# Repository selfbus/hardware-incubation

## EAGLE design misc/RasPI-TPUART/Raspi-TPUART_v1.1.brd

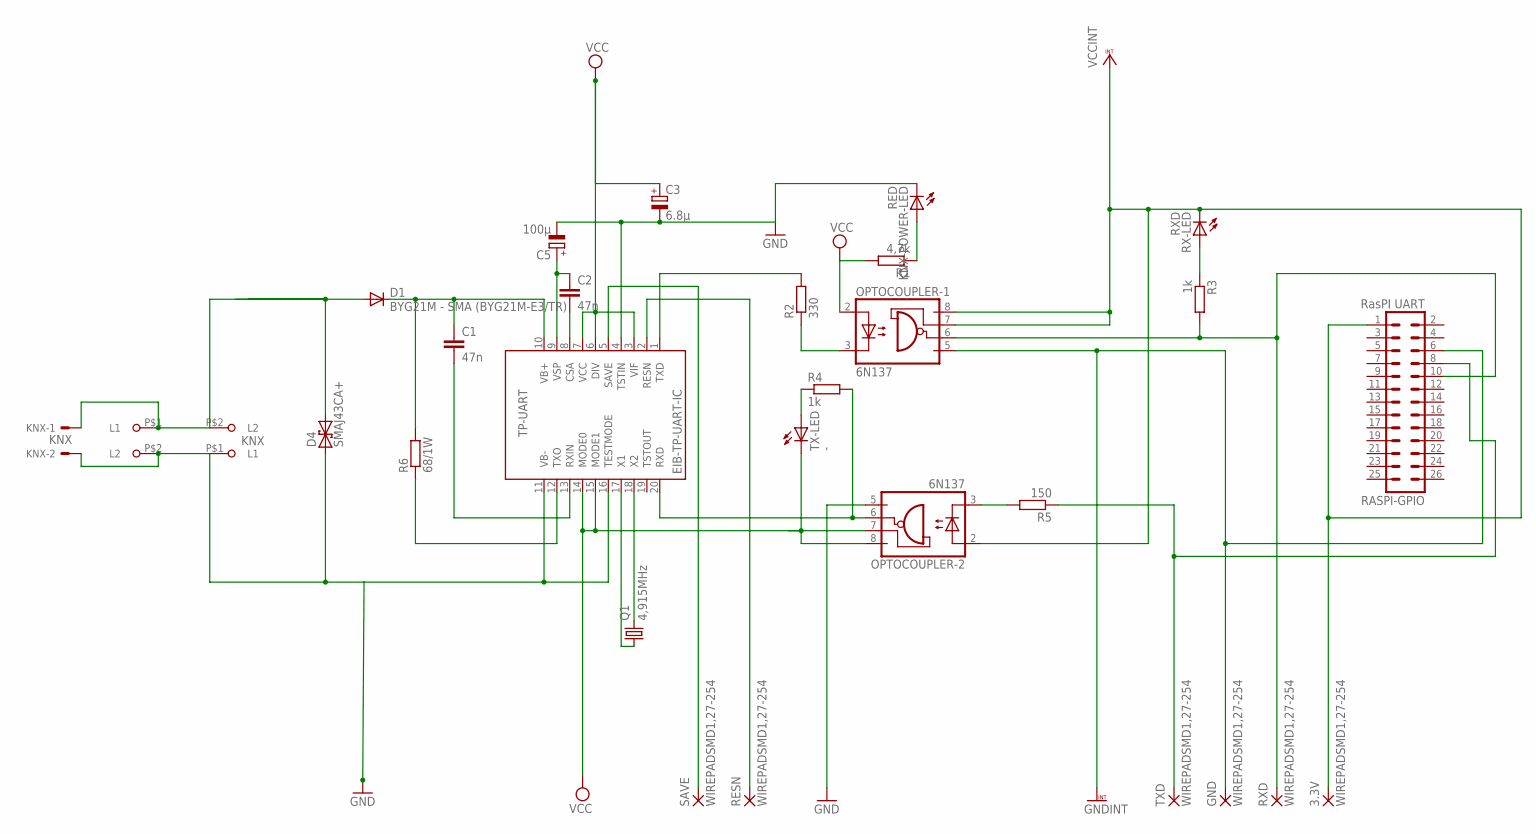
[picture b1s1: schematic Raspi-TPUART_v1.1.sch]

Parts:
3.3V: WIREPADSMD1,27-254; SMD1,27-2,54
C1, C2: 47n; C1206
C3: 6.8µ; CT7343
C5: 100µ; CT7343
D1: BYG21M - SMA (BYG21M-E3/TR); SMB
D4: SMAJ43CA+; DO214AA
EIB-TP-UART-IC: TP-UART; SOIC20
GND: WIREPADSMD1,27-254; SMD1,27-2,54
KNX: KNX; 22-23-2021
KNX-POWER-LED: RED; KA-3528ASYC
KNX_WAGO_243: 243-211
OPTOCOUPLER-1, OPTOCOUPLER-2: 6N137; DIL8-SMD
Q1: 4,915MHz; HC49UP
R1: 4,7k; M1206
R2: 330; M1206
R3, R4: 1k; M1206
R5: 150; M1206
R6: 68/1W; R2512
RASPI-GPIO: RasPI UART; MA13-2
RESN: WIREPADSMD1,27-254; SMD1,27-2,54
RX-LED: RXD; KA-3528ASYC
RXD: WIREPADSMD1,27-254; SMD1,27-2,54
SAVE: WIREPADSMD1,27-254; SMD1,27-2,54
TX-LED: -; KA-3528ASYC
TXD: WIREPADSMD1,27-254; SMD1,27-2,54
U$1: 243-211

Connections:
CSA: C2.2, EIB-TP-UART-IC.8 (CSA)
GND: C3.-, C5.-, D4.A (1), EIB-TP-UART-IC.4 (TSTIN), EIB-TP-UART-IC.11 (VB-), EIB-TP-UART-IC.16 (TESTMODE), KNX.2, KNX-POWER-LED.C, KNX_WAGO_243.P$1 (L1), OPTOCOUPLER-2.5 (GND), U$1.P$2 (L2)
GNDINT: GND.1, OPTOCOUPLER-1.5 (GND), RASPI-GPIO.6
KNX+: D1.A, D4.C (2), KNX.1, KNX_WAGO_243.P$2 (L2), U$1.P$1 (L1)
unnamed: R3.1, RX-LED.A
unnamed: R4.1, TX-LED.A
unnamed: OPTOCOUPLER-2.3 (C), R5.2
unnamed: KNX-POWER-LED.A, R1.1
RASPI_RXD: OPTOCOUPLER-1.6 (VO), R3.2, RASPI-GPIO.10, RXD.1
RASPI_TXD: R5.1, RASPI-GPIO.8, TXD.1
RESN: EIB-TP-UART-IC.2 (RESN), RESN.1
RXD: EIB-TP-UART-IC.20 (RXD), OPTOCOUPLER-2.6 (VO), R4.2
RXIN: C1.2, EIB-TP-UART-IC.13 (RXIN)
SAVE: EIB-TP-UART-IC.5 (SAVE), SAVE.1
TXD: EIB-TP-UART-IC.1 (TXD), R2.2
TXD1: OPTOCOUPLER-1.3 (C), R2.1
TXO: EIB-TP-UART-IC.12 (TXO), R6.1
VB+: C1.1, D1.C, EIB-TP-UART-IC.10 (VB+), R6.2
VCC: C3.+, EIB-TP-UART-IC.3 (VIF), EIB-TP-UART-IC.6 (DIV), EIB-TP-UART-IC.7 (VCC), EIB-TP-UART-IC.14 (MODE0), EIB-TP-UART-IC.15 (MODE1), OPTOCOUPLER-1.2 (A), OPTOCOUPLER-2.7 (VE), OPTOCOUPLER-2.8 (VCC), R1.2, TX-LED.C
VCCINT: 3.3V.1, OPTOCOUPLER-1.7 (VE), OPTOCOUPLER-1.8 (VCC), OPTOCOUPLER-2.2 (A), RASPI-GPIO.1, RX-LED.C
VSP: C2.1, C5.+, EIB-TP-UART-IC.9 (VSP)
X1: EIB-TP-UART-IC.17 (X1), Q1.1
X2: EIB-TP-UART-IC.18 (X2), Q1.2

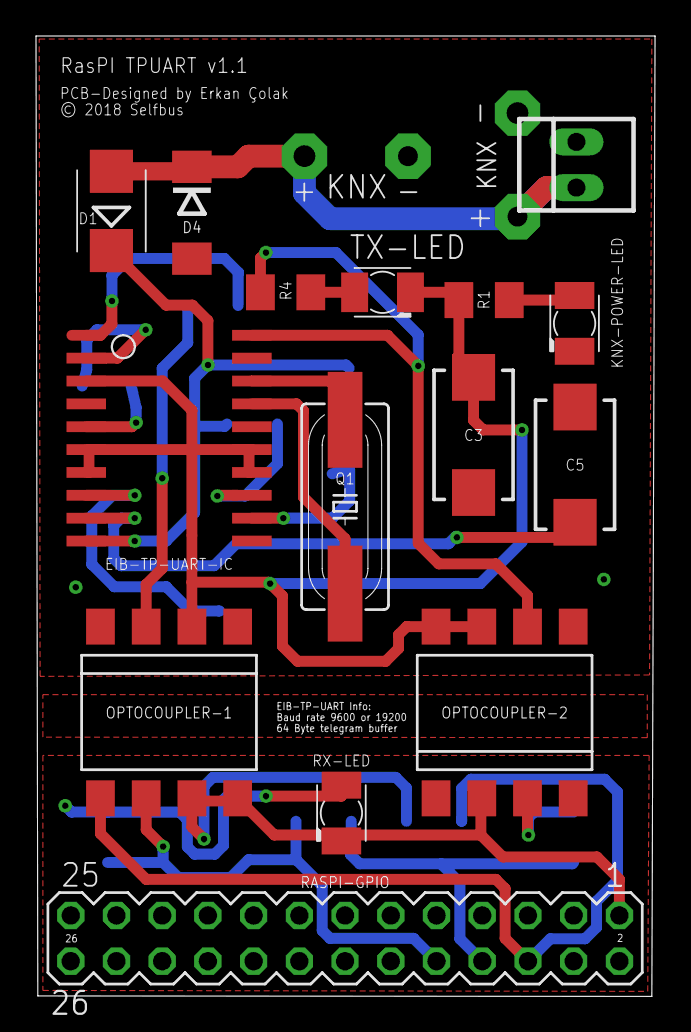
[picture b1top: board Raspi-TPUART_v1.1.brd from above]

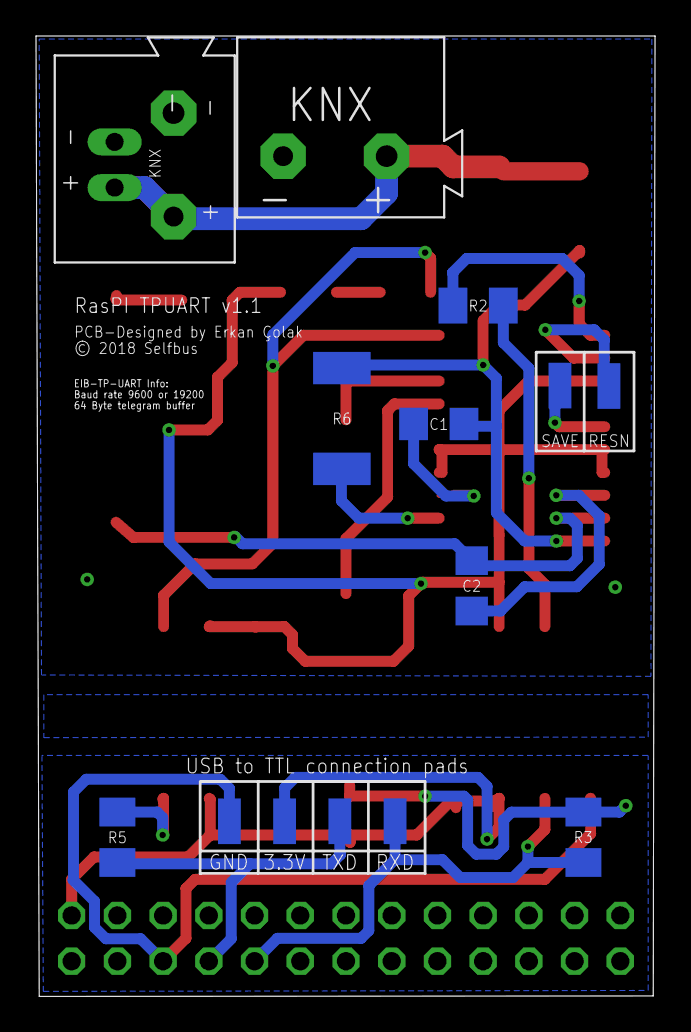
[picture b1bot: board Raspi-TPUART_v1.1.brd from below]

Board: 2 copper layers, 34.4 x 53.4 mm, 29 parts (14 on the bottom side), 23 nets.

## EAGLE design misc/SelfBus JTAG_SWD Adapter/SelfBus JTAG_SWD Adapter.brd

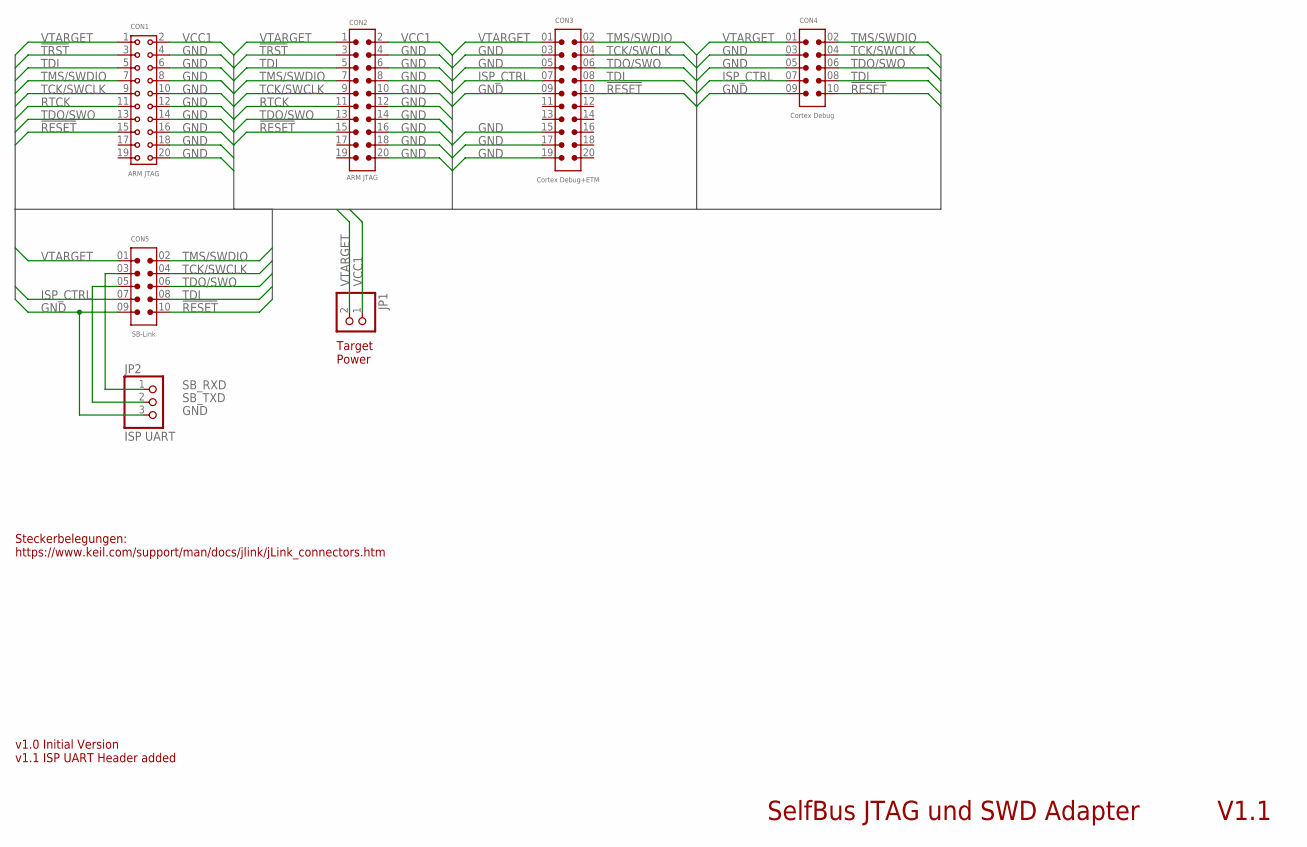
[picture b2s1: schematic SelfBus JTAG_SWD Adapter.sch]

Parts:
CON1: ARM JTAG; SAMTEC-SSQ-110-02-X-D-RA; MOUSER# 200-SSQ11002TDRA; LCSC2# C124406
CON2: ARM JTAG; 61202021721; MOUSER# 710-61202021721; LCSC3# C9144
CON3: Cortex Debug+ETM; SAMTEC_SHF-110-01-L-D-TH; MOUSER# 200-SHF11001LDTH
CON4: Cortex Debug; SAMTEC_SHF-105-01-X-D-TH; MOUSER# 200-SHF10501LDTH; LCSC2# C239059
CON5: SB-Link; SAMTEC-LTMM-105-02-T-D; MOUSER# 200-LTMM10502TD; LCSC3# C5661
JP1: Target Power; 1X02
JP2: ISP UART; 1X03

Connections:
!RESET: CON1.15, CON2.15, CON3.10, CON4.10, CON5.10
!TRST: CON1.3, CON2.3
GND: CON1.4, CON1.6, CON1.8, CON1.10, CON1.12, CON1.14, CON1.16, CON1.18, CON1.20, CON2.4, CON2.6, CON2.8, CON2.10, CON2.12, CON2.14, CON2.16, CON2.18, CON2.20, CON3.03 (3), CON3.05 (5), CON3.09 (9), CON3.15, CON3.17, CON3.19, CON4.03 (3), CON4.05 (5), CON4.09 (9), CON5.09 (9), JP2.3
ISP_CTRL: CON3.07 (7), CON4.07 (7), CON5.07 (7)
RTCK: CON1.11, CON2.11
SB_RXD: CON5.03 (3), JP2.1
SB_TXD: CON5.05 (5), JP2.2
TCK/SWCLK: CON1.9, CON2.9, CON3.04 (4), CON4.04 (4), CON5.04 (4)
TDI: CON1.5, CON2.5, CON3.08 (8), CON4.08 (8), CON5.08 (8)
TDO/SWO: CON1.13, CON2.13, CON3.06 (6), CON4.06 (6), CON5.06 (6)
TMS/SWDIO: CON1.7, CON2.7, CON3.02 (2), CON4.02 (2), CON5.02 (2)
VCC1: CON1.2, CON2.2, JP1.1
VTARGET: CON1.1, CON2.1, CON3.01 (1), CON4.01 (1), CON5.01 (1), JP1.2

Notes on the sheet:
SelfBus JTAG und SWD Adapter
V1.1
Target Power
Steckerbelegungen: https://www.keil.com/support/man/docs/jlink/jLink_connectors.htm
v1.0 Initial Version v1.1 ISP UART Header added

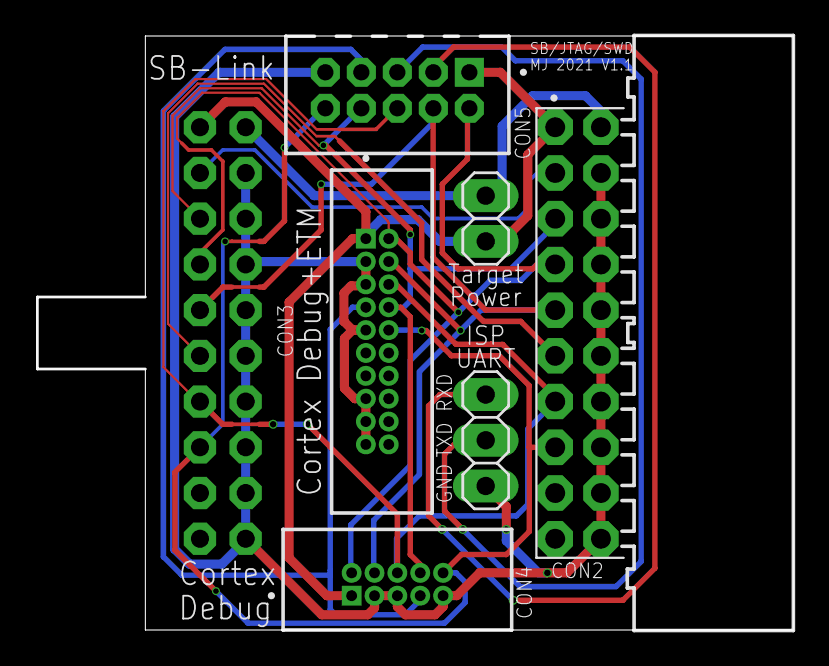
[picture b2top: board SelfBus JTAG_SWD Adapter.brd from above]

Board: 2 copper layers, 42.0 x 33.0 mm, 7 parts (1 on the bottom side), 13 nets.

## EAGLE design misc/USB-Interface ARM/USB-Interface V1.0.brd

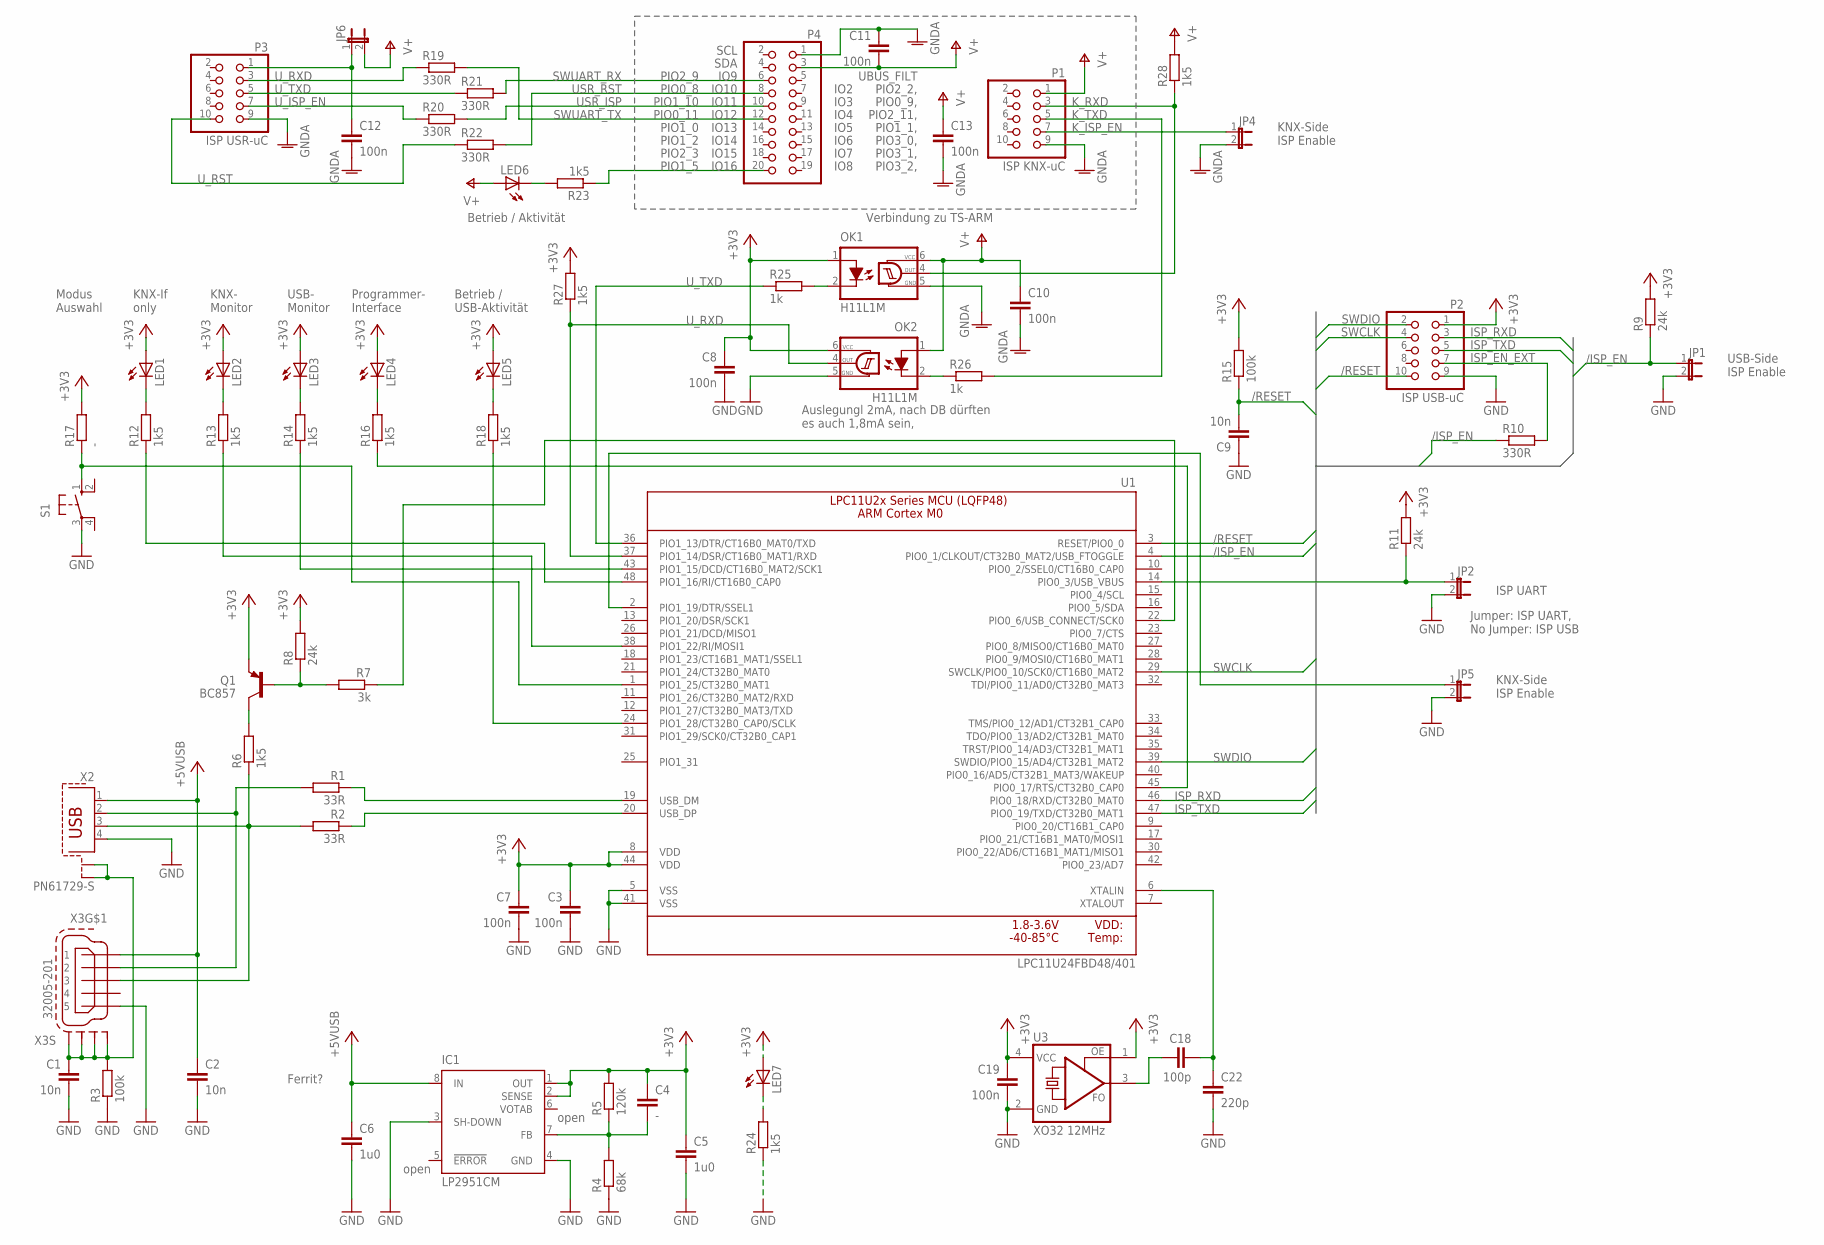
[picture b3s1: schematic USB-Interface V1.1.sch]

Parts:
C1, C2, C9: 10n; R0805M
C3, C7, C8, C10, C11, C12, C13, C19: 100n; R0805M
C4: -; R0805M
C5, C6: 1u0; R0805M
C18: 100p; R0805M
C22: 220p; R0805M
IC1: LP2951CM; SO08
JP1, JP2, JP4, JP5, JP6: JP1E; JP1
LED1, LED2, LED3, LED4, LED5, LED6, LED7: LEDSMT1206; 1206
OK1, OK2: H11L1M; DIL06S
P1: ISP KNX-uC; 2X05M
P2: ISP USB-uC; 2X05M
P3: ISP USR-uC; 2X05M
P4: PINHD-2X10/90; 2X10/90
Q1: BC857; SOT23-BEC
R1, R2: 33R; R0805M
R3, R15: 100k; R0805M
R4: 68k; R0805M
R5: 120k; R0805M
R6, R12, R13, R14, R16, R18, R23, R24, R27, R28: 1k5; R0805M
R7: 3k; R0805M
R8, R9, R11: 24k; R0805M
R10, R19, R20, R21, R22: 330R; R0805M
R17: -; R0805M
R25, R26: 1k; R0805M
S1: 10-XXSMD; B3F-10XX_SMD
U1: LPC11U24FBD48/401; LQFP48
U3: XO32 12MHz; ASF
X2: PN61729-S
X3: 32005-201

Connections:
+3V3: C3.1, C4.1, C5.1, C7.1, C8.1, C19.1, IC1.1 (OUT), IC1.2 (SENSE), LED1.A, LED2.A, LED3.A, LED4.A, LED5.A, LED7.A, OK1.1 (A), OK2.6 (VCC), P2.1, Q1.E, R5.2, R8.2, R9.2, R11.2, R15.2, R17.2, R27.2, U1.8 (VDD), U1.44 (VDD), U3.1 (OE), U3.4 (VCC)
+5V: C2.1, C6.1, IC1.8 (IN), X2.1, X3.1
/ISP_EN: JP1.1, R9.1, R10.1, U1.4 (PIO0_1/CLKOUT/CT32B0_MAT2/USB_FTOGGLE)
/RESET: C9.2, P2.10, R15.1, U1.3 (RESET/PIO0_0)
GND: C1.2, C2.2, C3.2, C5.2, C6.2, C7.2, C8.2, C9.1, C19.2, C22.2, IC1.3 (SH-DOWN), IC1.4 (GND), JP1.2, JP2.2, JP5.2, OK2.5 (GND), P2.9, R3.1, R4.1, R24.1, S1.3, U1.5 (VSS), U1.41 (VSS), U3.2 (GND), X2.4, X3.5
GNDA: C10.2, C11.1, C12.2, C13.2, JP4.2, OK1.5 (GND), P1.9, P3.9, P4.1
ISP_EN1: JP2.1, R11.1, U1.14 (PIO0_3/USB_VBUS)
ISP_EN_EXT: P2.7, R10.2
ISP_RXD: P2.3, U1.46 (PIO0_18/RXD/CT32B0_MAT0)
ISP_TXD: P2.5, U1.47 (PIO0_19/TXD/CT32B0_MAT1)
K_ISP_EN: JP4.1, P1.7
K_RXD: OK1.4 (OUT), P1.3, R28.1
K_TXD: P1.5, R26.2
unnamed: R1.1, U1.19 (USB_DM)
unnamed: R2.1, U1.20 (USB_DP)
unnamed: JP5.1, U1.2 (PIO1_19/DTR/SSEL1)
unnamed: R1.2, X2.2, X3.2
unnamed: R2.2, R6.1, X2.3, X3.3
unnamed: C1.1, R3.2, X2.S1, X2.S2, X3.M1 (S1), X3.M2 (S2), X3.M3 (S3), X3.M4 (S4)
unnamed: Q1.B, R7.2, R8.1
unnamed: C4.2, IC1.7 (FB), R4.2, R5.1
unnamed: Q1.C, R6.2
unnamed: R7.1, U1.22 (PIO0_6/USB_CONNECT/SCK0)
unnamed: LED6.C, R23.2
unnamed: P4.20, R23.1
unnamed: R17.1, S1.1 (S), U1.1 (PIO1_25/CT32B0_MAT1)
unnamed: LED1.C, R12.2
unnamed: LED2.C, R13.2
unnamed: C18.1, U3.3 (FO)
unnamed: LED3.C, R14.2
unnamed: LED4.C, R16.2
unnamed: R16.1, U1.45 (PIO0_17/RTS/CT32B0_CAP0)
unnamed: R14.1, U1.43 (PIO1_15/DCD/CT16B0_MAT2/SCK1)
unnamed: C18.2, C22.1, U1.6 (XTALIN)
unnamed: R13.1, U1.38 (PIO1_22/RI/MOSI1)
unnamed: R12.1, U1.48 (PIO1_16/RI/CT16B0_CAP0)
unnamed: LED7.C, R24.2
unnamed: R18.1, U1.24 (PIO1_28/CT32B0_CAP0/SCLK)
unnamed: LED5.C, R18.2
unnamed: P3.7, R20.1
unnamed: C12.1, JP6.1, P3.1
unnamed: OK1.2 (C), R25.2
unnamed: P3.10, R22.1
unnamed: P3.5, R21.1
unnamed: P3.3, R19.1
unnamed: OK2.2 (C), R26.1
SWCLK: P2.4, U1.29 (SWCLK/PIO0_10/SCK0/CT16B0_MAT2)
SWDIO: P2.2, U1.39 (SWDIO/PIO0_15/AD4/CT32B1_MAT2)
SWUART_RX: P4.6, R21.2
SWUART_TX: P4.12, R19.2
USR_ISP: P4.10, R20.2
USR_RST: P4.8, R22.2
U_RXD: OK2.4 (OUT), R27.1, U1.37 (PIO1_14/DSR/CT16B0_MAT1/RXD)
U_TXD: R25.1, U1.36 (PIO1_13/DTR/CT16B0_MAT0/TXD)
V+: C10.1, C11.2, C13.1, JP6.2, LED6.A, OK1.6 (VCC), OK2.1 (A), P1.1, P4.3, R28.2

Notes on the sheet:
open
Ferrit?
USB-Side ISP Enable
ISP UART
Jumper: ISP UART, No Jumper: ISP USB
KNX-If only
KNX- Monitor
USB- Monitor
Programmer- Interface
Modus Auswahl
SCL
SDA
IO9
IO10
IO11
IO12
IO13
IO14
IO15
IO16
PIO2_9
PIO0_8
PIO1_10
PIO0_11
PIO1_0
PIO1_2
PIO2_3
PIO1_5
IO2
IO3
IO4
IO5
IO6
IO7
IO8
PIO2_2,
PIO0_9,
PIO2_11,
PIO1_1,
PIO3_0,

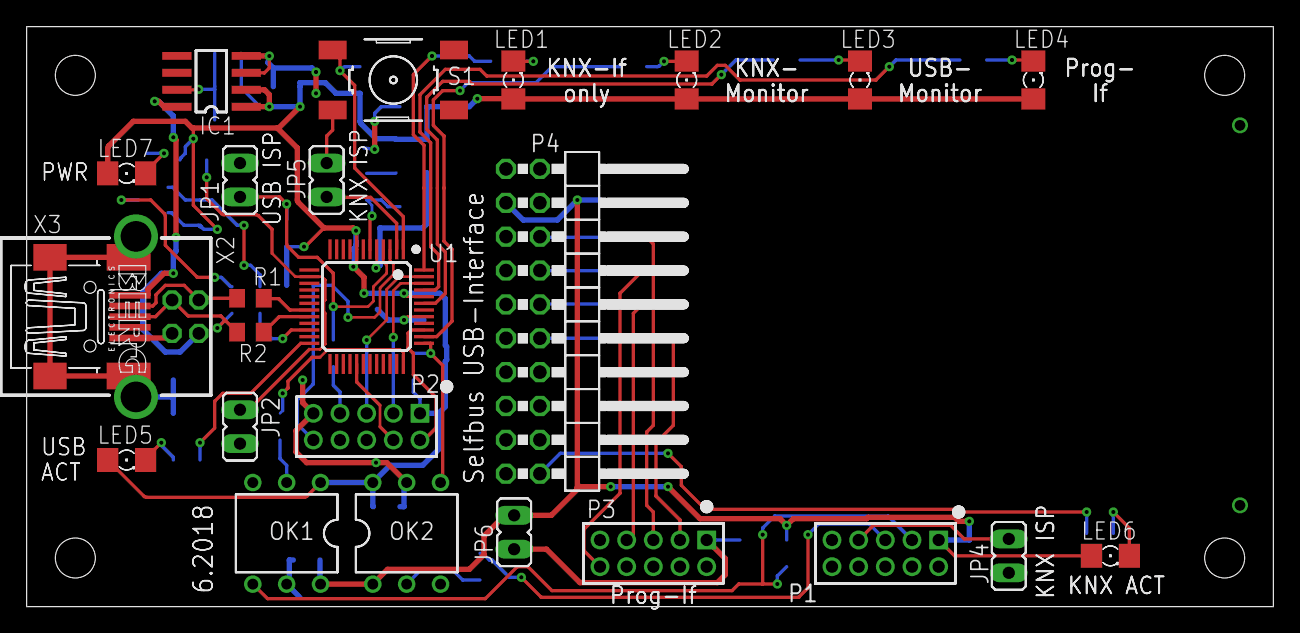
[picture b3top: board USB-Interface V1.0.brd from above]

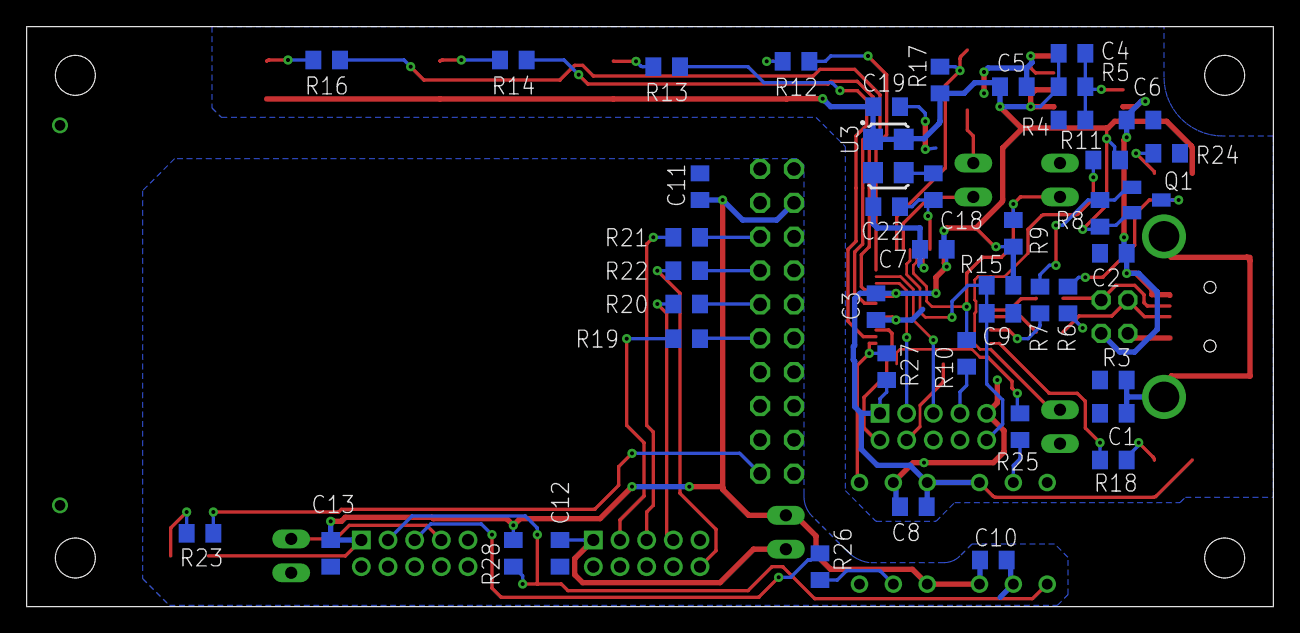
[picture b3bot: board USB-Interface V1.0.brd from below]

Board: 2 copper layers, 93.5 x 43.5 mm, 69 parts (44 on the bottom side), 55 nets.

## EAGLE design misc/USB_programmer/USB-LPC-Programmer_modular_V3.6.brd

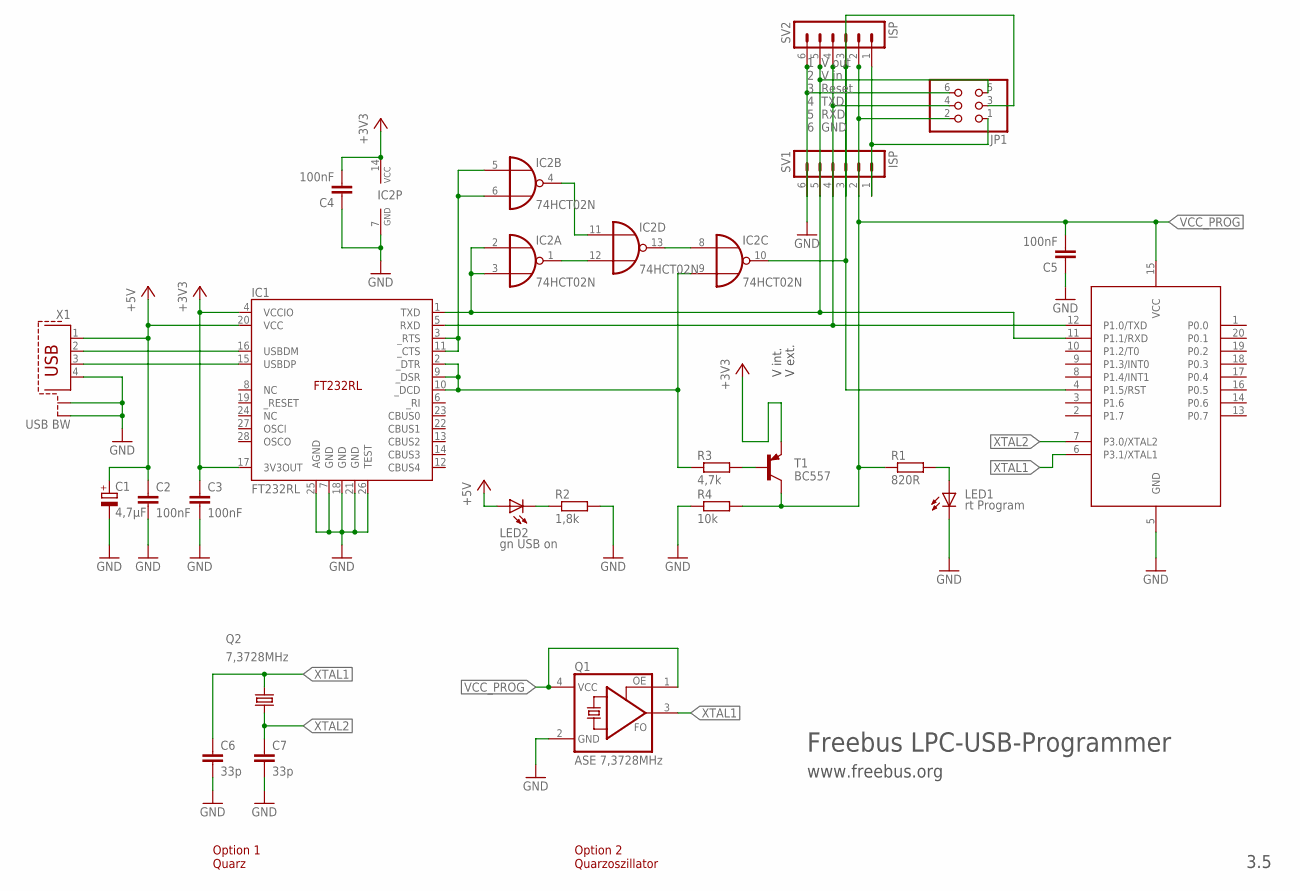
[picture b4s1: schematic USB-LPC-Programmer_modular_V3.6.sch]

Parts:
89LPC922: LPC-Sockel; DIL20
C1: 4,7µF; E2,5-6
C2, C3, C4, C5: 100nF; C050-024X044
C6, C7: 33p; C025-024X044
IC1: FT232RL; SSOP-28
IC2: 74HCT02N; DIL14
JP1: PINHD-2X3; 2X03
LED1: rt Program; LED3MM
LED2: gn USB on; LED3MM
Q1: ASE 7,3728MHz; ASF
Q2: 7,3728MHz; HC49/S
R1: 820R; 0207/7
R2: 1,8k; 0207/7
R3: 4,7k; 0204/7
R4: 10k; 0207/7
SV1, SV2: ISP; MA06-1
T1: BC557; TO92
X1: USB BW; PN61729-S

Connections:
+3V3: C3.1, C4.2, IC1.4 (VCCIO), IC1.17 (3V3OUT), IC2.14 (VCC), T1.1 (E)
+5V: C1.+, C2.1, IC1.20 (VCC), LED2.A, X1.1
GND: 89LPC922.5 (GND), C1.-, C2.2, C3.2, C4.1, C5.1, C6.2, C7.2, IC1.7 (GND), IC1.18 (GND), IC1.21 (GND), IC1.25 (AGND), IC1.26 (TEST), IC2.7 (GND), JP1.6, LED1.K (C), Q1.2 (GND), R2.2, R4.1, SV1.6, SV2.6, X1.4, X1.S1, X1.S2
unnamed: JP1.1, SV1.1, SV2.1
unnamed: IC2.4 (O), IC2.11 (I0)
unnamed: 89LPC922.4 (P1.5/RST), IC2.10 (O), JP1.3, SV1.3, SV2.3
unnamed: LED2.K (C), R2.1
unnamed: IC2.1 (O), IC2.12 (I1)
unnamed: LED1.A, R1.2
unnamed: IC1.16 (USBDM), X1.2
unnamed: IC2.8 (I0), IC2.13 (O)
unnamed: IC1.15 (USBDP), X1.3
unnamed: R3.2, T1.2 (B)
PROG_PWR_ON: IC1.2 (_DTR), IC1.9 (_DSR), IC1.10 (_DCD), IC2.9 (I1), R3.1
RTS_CTS1: IC1.3 (_RTS), IC1.11 (_CTS), IC2.5 (I0), IC2.6 (I1)
USB_RX: 89LPC922.12 (P1.0/TXD), IC1.5 (RXD), JP1.4, SV1.4, SV2.4
USB_TX: 89LPC922.11 (P1.1/RXD), IC1.1 (TXD), IC2.2 (I0), IC2.3 (I1), JP1.5, SV1.5, SV2.5
VCC_PROG: 89LPC922.15 (VCC), C5.2, JP1.2, Q1.1 (OE), Q1.4 (VCC), R1.1, R4.2, SV1.2, SV2.2, T1.3 (C)
XTAL1: 89LPC922.6 (P3.1/XTAL1), C6.1, Q1.3 (FO), Q2.2
XTAL2: 89LPC922.7 (P3.0/XTAL2), C7.1, Q2.1

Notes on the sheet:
Freebus LPC-USB-Programmer
www.freebus.org
3.5
2 V in
3 Reset
4 TXD
5 RXD
6 GND
1 V out
Option 1 Quarz
Option 2 Quarzoszillator
V int.
V ext.

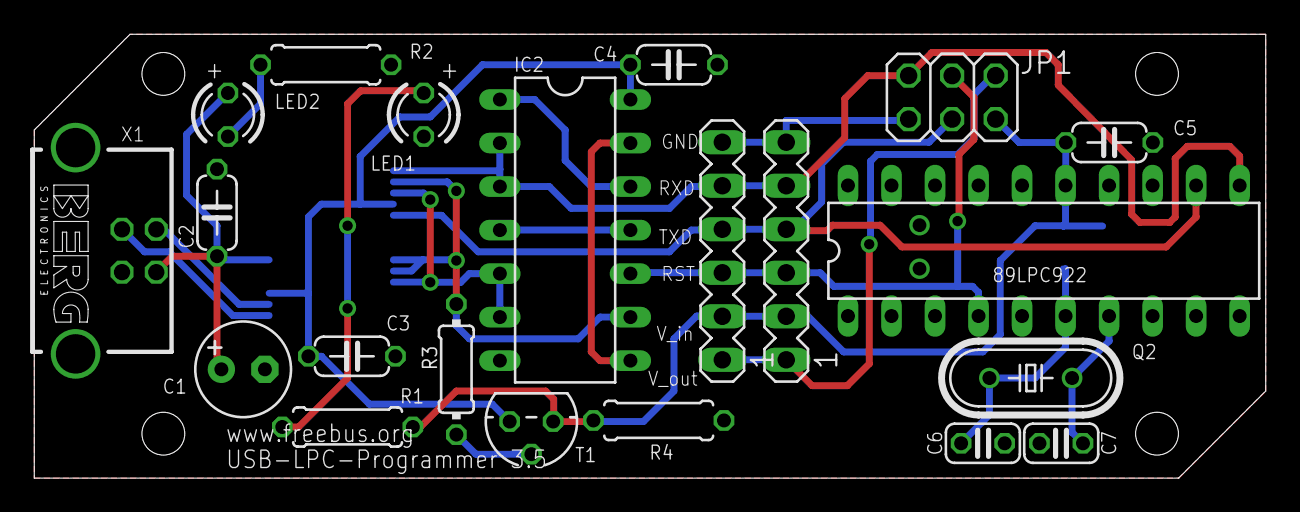
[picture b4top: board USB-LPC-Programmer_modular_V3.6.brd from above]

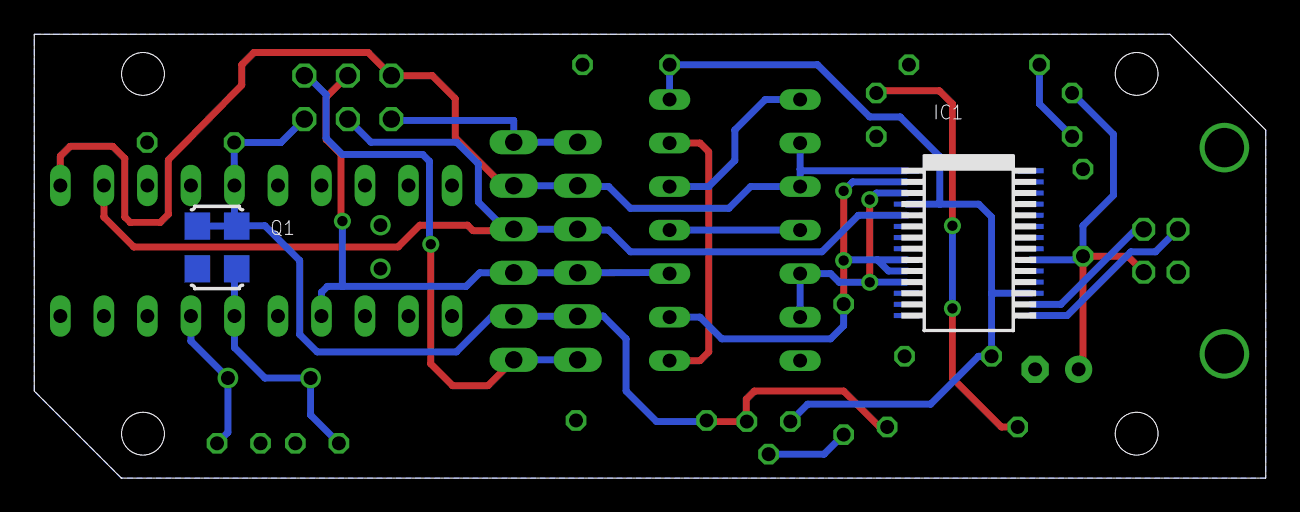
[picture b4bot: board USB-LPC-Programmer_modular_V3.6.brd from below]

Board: 2 copper layers, 71.9 x 25.9 mm, 23 parts (2 on the bottom side), 20 nets.

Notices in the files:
misc/RasPI-TPUART/Raspi-TPUART_v1.1.brd:
© 2018 Selfbus
